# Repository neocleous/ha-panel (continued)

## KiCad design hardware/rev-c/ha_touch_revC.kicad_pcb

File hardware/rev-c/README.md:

# HA Panel — Touch Board rev C

**This is the touch board of the first panel (v1), which is built and in use.** The new panel uses touch board
rev D, in [`../touch-board/`](../touch-board/).

Capacitive 4-button touch board for the wall-mounted Home Assistant panel.
Carries the touch controller and acts as the wiring hub for the panel's I2C
sensor breakouts. Designed 2026-07; fabricated at JLCPCB.

Rev C is a ground-up redesign (KiCad 7, programmatically generated) replacing
the rev-A/rev-B EasyEDA design.

## Specifications

| Parameter | Value |
|---|---|
| Dimensions | 100 x 44 mm, rounded corners r2, 1.6 mm FR-4 |
| Layers | 2 (front: electrodes + bus, back: all components) |
| Finish | ENIG, green mask, white silk |
| Holes | None (tented vias only) — front face is completely flat |
| Touch controller | AT42QT1070-SSUR (SOIC-14), I2C addr 0x1B |
| Electrodes | 4x Ø12 mm top copper, mask-covered (intentional — no exposed metal), 24 mm pitch |
| I2C | No on-board pull-ups; bus relies on host (Pi 1.8k) + breakout pull-ups |

## Design notes / changes vs rev A

- **MODE (pin 2) tied to GND** — hard requirement for I2C mode. Floating MODE
  was the probable root cause of rev A never appearing at 0x1B.
- **4.7k series resistors (R1–R4) added in each KEY sense line** per
  AT42QT1070 datasheet §3.1 (ESD/RFI). Rev A had none.
- **4.7k series resistors in SDA/SCL removed** — with the Pi's 1.8k hardware
  pull-ups they broke logic levels (V_OL ≈ 2.4 V at the host).
- Unused pins (KEY4–6, RESET#, CHANGE#) left unconnected per datasheet;
  disable keys 4–6 in software (AVE/AKS = 0).
- All silkscreen is human-readable: every part carries designator + value,
  every wire pad is net-labelled, U1 has a pin-1 dot.

## Wire pad clusters (bottom edge, viewed from the back)

Left to right: **HOST (PI)** · **BME680** · **VL53L0X** · **VEML6030**
Each cluster: `VCC  GND  SDA  SCL` (labelled). Pads 2x3 mm, 3.5 mm pitch,
sized for 24 AWG (power) / 28 AWG (signal) silicone stranded wire.

All three sensor clusters are parallel drops on the same I2C bus
(0x77 / 0x29 / 0x48; controller at 0x1B — no conflicts).

## Electrode / key mapping

Viewed from the FRONT of the panel, left to right the electrodes are
**KEY3, KEY2, KEY1, KEY0** (routing-optimised order). Map keys to actions
in `sensor-daemon` accordingly.

## Assembly

1. Stencil (bottom side, 0.12 mm) + Sn63/Pb37 no-clean paste (SMD291AXT4).
   Paste apertures exist only for U1, R1–R4, C1, C2 — wire pads are
   intentionally paste-free.
2. Place: U1 (mind the pin-1 dot), 4x 4k7 0402, C1 100n 0402, C2 10u 0603.
3. Hot air ~320 °C, low-mid airflow, until reflow + a few seconds.
4. Solder harness wires to the clusters with an iron (pre-tin wire + pad).
5. Bring-up: power via HOST cluster, then `sudo i2cdetect -y 1` on the Pi —
   0x1B present validates MODE strap, solder and bus in one shot.

## Files

- `ha_touch_revC.kicad_pcb` — board source (KiCad 7). DRC-clean. This is
  the canonical file; the fabrication set regenerates from it exactly:
  `kicad-cli pcb export gerbers ha_touch_revC.kicad_pcb -o gerbers/ \
   --layers "F.Cu,B.Cu,F.Mask,B.Mask,F.SilkS,B.SilkS,B.Paste,Edge.Cuts" \
   --subtract-soldermask` plus
  `kicad-cli pcb export drill --format excellon --excellon-separate-th`.
  The zip as actually ordered (2026-07-26) is archived offline.
- `BOM.csv` — bill of materials with DigiKey part numbers.

JLCPCB order settings: 2 layer, 1.6 mm, ENIG, tented vias, remove mark,
flying-probe test; stencil bottom-only, custom 190x190 mm.

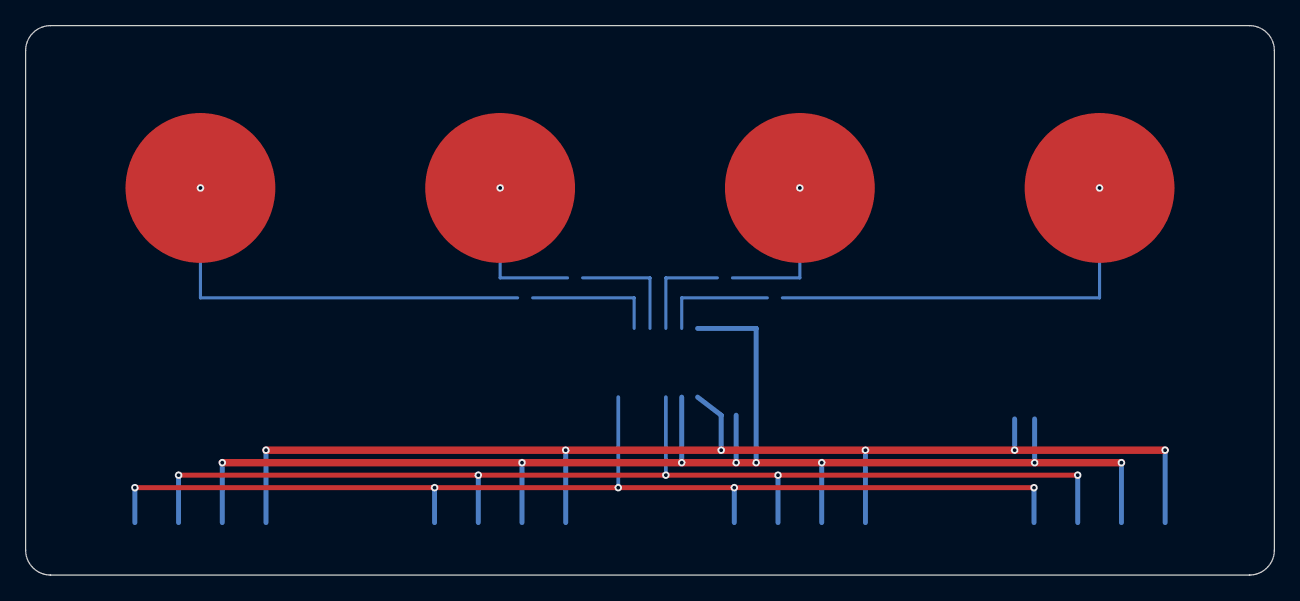
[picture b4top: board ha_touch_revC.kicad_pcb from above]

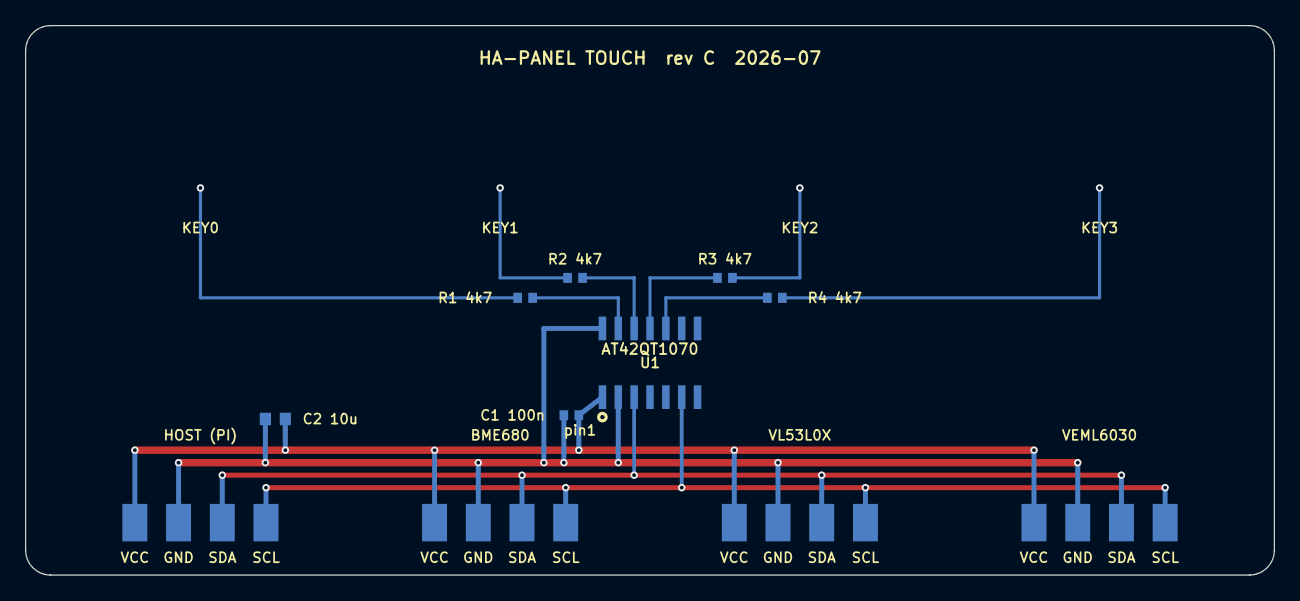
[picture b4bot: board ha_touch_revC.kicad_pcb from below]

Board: 2 copper layers, 100.0 x 44.0 mm, 15 parts (11 on the bottom side), 12 nets.

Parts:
C1: C1
C2: C2
E0: E0
E1: E1
E2: E2
E3: E3
J1: J1
J2: J2
J3: J3
J4: J4
R1: R1
R2: R2
R3: R3
R4: R4
U1: U1

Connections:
GND: C1.2, C2.2, J1.2, J2.2, J3.2, J4.2, U1.2, U1.14
KEY0: R1.1, U1.13
KEY1: R2.1, U1.12
KEY2: R3.2, U1.11
KEY3: R4.2, U1.10
SCL: J1.4, J2.4, J3.4, J4.4, U1.6
SDA: J1.3, J2.3, J3.3, J4.3, U1.3
SENSE0: E0.1, R1.2
SENSE1: E1.1, R2.2
SENSE2: E2.1, R3.1
SENSE3: E3.1, R4.1
VCC: C1.1, C2.1, J1.1, J2.1, J3.1, J4.1, U1.1

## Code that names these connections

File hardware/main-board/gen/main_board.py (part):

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        '  STANDBY (Pi 3V3 off, 5 V on, HAT+ spec 2.2): LDO off -> no back-feed through I2C; amp muted by R17.',
        'R26/R27: amp logic rail 3V3_AMP from the LDO (default, R26) or from the Pi 3V3 (R27): TAS5756M VIH = 0.9 x DVDD',
        '  (SLAS988B 7.3) and TI advises driving its inputs from the DVDD supply; LDO +-1 % (SBVS186H) vs Pi 3V3 (not published).',
        'Pi pins: 3/5 SDA/SCL (GPIO2/3, 1.8 k pull-ups on the Pi); 8/10 TXD/RXD (GPIO14/15, uart0);',
        '  12/35/38/40 = GPIO18/19/20/21 I2S BCLK/LRCLK/DIN/DOUT; 15 = GPIO22 amp mute (rpi-digiampplus).',
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        'Sensor branch 3V3_SENS (F4 0.2 A PTC): J6 touch board, J10 BME680, J11 VEML6030 (one 1 x 4 header each, rev 3).',
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           footprint='Fuse:Fuse_2920_7451Metric',
           fields=F('2920L260/33DR', 'Littelfuse', '18-2920L260/33DRCT-ND', 'PTC 2.6 A hold (1.81 A at 60 C), 33 V, R1max 75 mOhm'))
    s.pwr_flag('PVDD', (66.04, 60.96))
    s.text('PVDD probe point: F5 pin 2 (2920 land, door-side face). No TP18.',
           88.9, 38.1, size=1.27)
    s.text('C101, C102, C122, C123: 4.7 uF 50 V X7R since 2026-11-17 (D192), not the 22 uF 35 V X5R of TI Table 22.\n'
           'At 20 V both keep about 1.9 uF (TDK DC-bias data).',
           101.6, 66.04, size=1.27)
    # PVDD decoupling (left side pins 6/7 and right side 41-43)
    for i, (ref, val, fp, spec) in enumerate([('C100', '0.1u 50V', C0603, '0.1 uF 50 V X7R 0603'),
                                              ('C101', '4.7u 50V', C0805, '4.7 uF 50 V X7R 0805'),
                                              ('C102', '4.7u 50V', C0805, '4.7 uF 50 V X7R 0805'),
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        # 2026-11-17 (D192): TDK 4.7 uF 50 V X7R in place of the 22 uF 35 V X5R; about 1.9 uF each at 20 V either way (TDK's curves)
        mpn = ('C2012X7R1H475K125AC', 'TDK', '445-C2012X7R1H475K125ACCT-ND') if val.startswith('4.7u') else ('', '', '')
        s.comp(ref, 'Device:C', val, (101.6 + i * 12.7, 53.34), nets={'1': 'PVDD', '2': 'GND'}, footprint=fp,
               fields=F(mpn[0], mpn[1], mpn[2], spec, 'PVDD pins 6/7 (C100-C102) and 41-43 (C121-C123): place at the pins'))
    s.comp('U100', 'ha_panel:TAS5756M', 'TAS5756MDCAR', (190.5, 129.54),
           nets={'23': 'I2S_BCLK', '25': 'I2S_LRCLK', '24': 'I2S_DOUT', '22': 'GND',
                 '16': 'I2C_SDA', '17': 'I2C_SCL', '26': 'GND', '20': 'GND',
                 '18': 'AMP_GPIO0', '19': 'AMP_GPIO1', '21': 'AMP_GPIO2',
                 '27': 'AMP_MUTE_N', '40': 'AMP_FAULT_N',
                 '30': '3V3_AMP', '31': '3V3_AMP', '14': '3V3_AMP', '28': 'DVDD_REG', '32': 'CP', '34': 'CN', '35': 'CPVSS',
                 '6': 'PVDD', '7': 'PVDD', '41': 'PVDD', '42': 'PVDD', '43': 'PVDD',
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    # control pins
    s.comp('R102', 'Device:R', '100k', (38.1, 106.68), nets={'1': '3V3_AMP', '2': 'AMP_FAULT_N'}, footprint=R0603,
           fields=F(spec='100 kOhm 1% 0603', note='SPK_FAULT pull-up (VOL spec uses 100 k)'))
    for i, (ref, net) in enumerate([('R103', 'AMP_GPIO0'), ('R104', 'AMP_GPIO1'), ('R105', 'AMP_GPIO2')]):
        s.comp(ref, 'Device:R', '100k', (55.88 + i * 12.7, 106.68), nets={'1': net, '2': 'GND'}, footprint=R0603,
               fields=F(spec='100 kOhm 1% 0603', note='unused GPIO held low'))
    tp(s, 'TP19', 'AMP_FAULT_N', 25.4, 106.68, 'FAULT')
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        'Overlay rpi-digiampplus: pcm5122@4c on i2c1, i2s_clk_producer, mute-gpios GPIO22 active high (driver sets 1 = unmute).',
        'Thermal pad: via array + paste windows 70-80 % of the pad area (SLAS988B 11.1.3.2) - footprint in block 2.',
        'No PVDD electrolytic at the amp (block 2, layout density): TI Table 22 says the 390 uF bulk "can be reduced or even removed";',
        '  C5 (120 uF on +20V) feeds PVDD through F5 (75 mOhm max, tau 9 us), plus 4 x 22 uF + 2 x 0.1 uF at the PVDD pins.']),
        25.4, 243.84)


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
